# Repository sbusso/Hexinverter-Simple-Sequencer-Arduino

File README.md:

# Hexinverter-Simple-Sequencer-Arduino
Modified Version of Hexinverter Simple Seq, using 2 arduino nano boards intstead of the logic boards

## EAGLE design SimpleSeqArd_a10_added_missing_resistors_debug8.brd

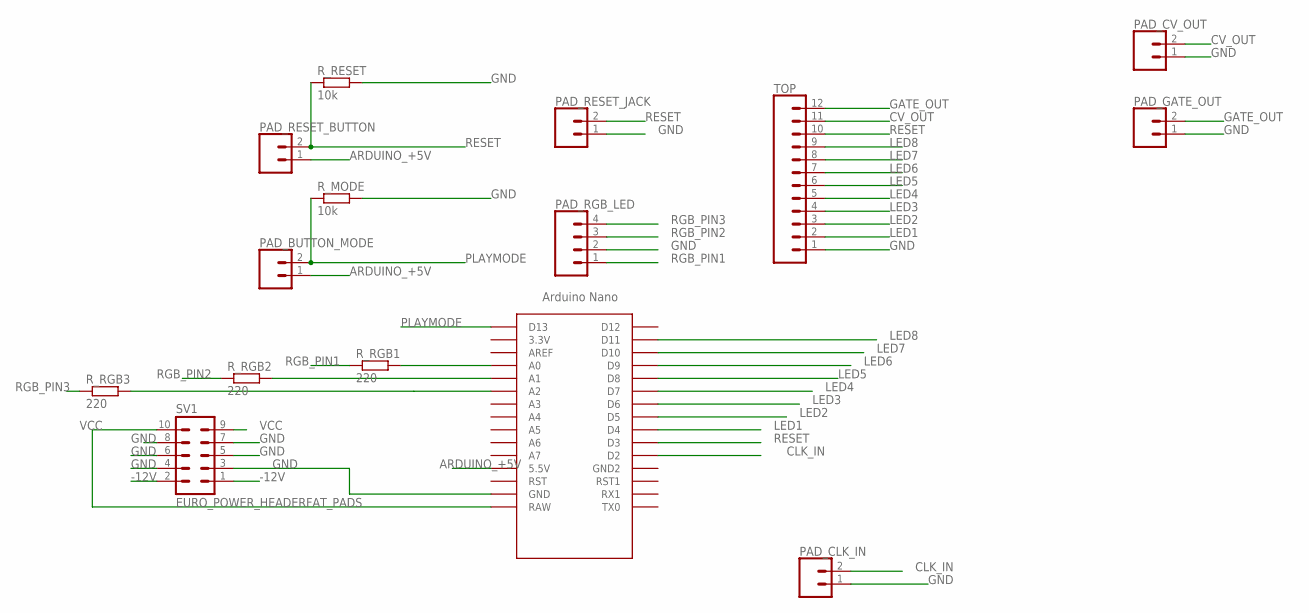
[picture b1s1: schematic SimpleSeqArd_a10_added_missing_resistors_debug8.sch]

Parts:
PAD_BUTTON_MODE: CONN_02PTH3; 1X02_LONGPADS
PAD_CLK_IN: CONN_02PTH3; 1X02_LONGPADS
PAD_CV_OUT: CONN_02PTH3; 1X02_LONGPADS
PAD_GATE_OUT: CONN_02PTH3; 1X02_LONGPADS
PAD_RESET_BUTTON: CONN_02PTH3; 1X02_LONGPADS
PAD_RESET_JACK: CONN_02PTH3; 1X02_LONGPADS
PAD_RGB_LED: CONN_04LONGPADS; 1X04_LONGPADS
R_MODE: 10k; VERTICAL_RESISTOR
R_RESET: 10k; VERTICAL_RESISTOR
R_RGB1, R_RGB2, R_RGB3: 220; VERTICAL_RESISTOR
SV1: EURO_POWER_HEADERFAT_PADS; EURO_PWR_HEADER_FAT
TOP: CONN_12LONGPADS; 1X12_LONGPADS
U$1: NANO

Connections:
-12V: SV1.1, SV1.2
ARDUINO_+5V: PAD_BUTTON_MODE.1, PAD_RESET_BUTTON.1, U$1.5V (5.5V)
CLK_IN: PAD_CLK_IN.2, U$1.D2
CV_OUT: PAD_CV_OUT.2, TOP.11
GATE_OUT: PAD_GATE_OUT.2, TOP.12
GND: PAD_CLK_IN.1, PAD_CV_OUT.1, PAD_GATE_OUT.1, PAD_RESET_JACK.1, PAD_RGB_LED.2, R_MODE.2, R_RESET.2, SV1.3, SV1.4, SV1.5, SV1.6, SV1.7, SV1.8, TOP.1, U$1.GND
LED1: TOP.2, U$1.D4
LED2: TOP.3, U$1.D5
LED3: TOP.4, U$1.D6
LED4: TOP.5, U$1.D7
LED5: TOP.6, U$1.D8
LED6: TOP.7, U$1.D9
LED7: TOP.8, U$1.D10
LED8: TOP.9, U$1.D11
unnamed: R_RGB1.2, U$1.A0
unnamed: R_RGB2.2, U$1.A1
unnamed: R_RGB3.2, U$1.A2
PLAYMODE: PAD_BUTTON_MODE.2, R_MODE.1, U$1.D13
RESET: PAD_RESET_BUTTON.2, PAD_RESET_JACK.2, R_RESET.1, TOP.10, U$1.D3
RGB_PIN1: PAD_RGB_LED.1, R_RGB1.1
RGB_PIN2: PAD_RGB_LED.3, R_RGB2.1
RGB_PIN3: PAD_RGB_LED.4, R_RGB3.1
VCC: SV1.9, SV1.10, U$1.RAW

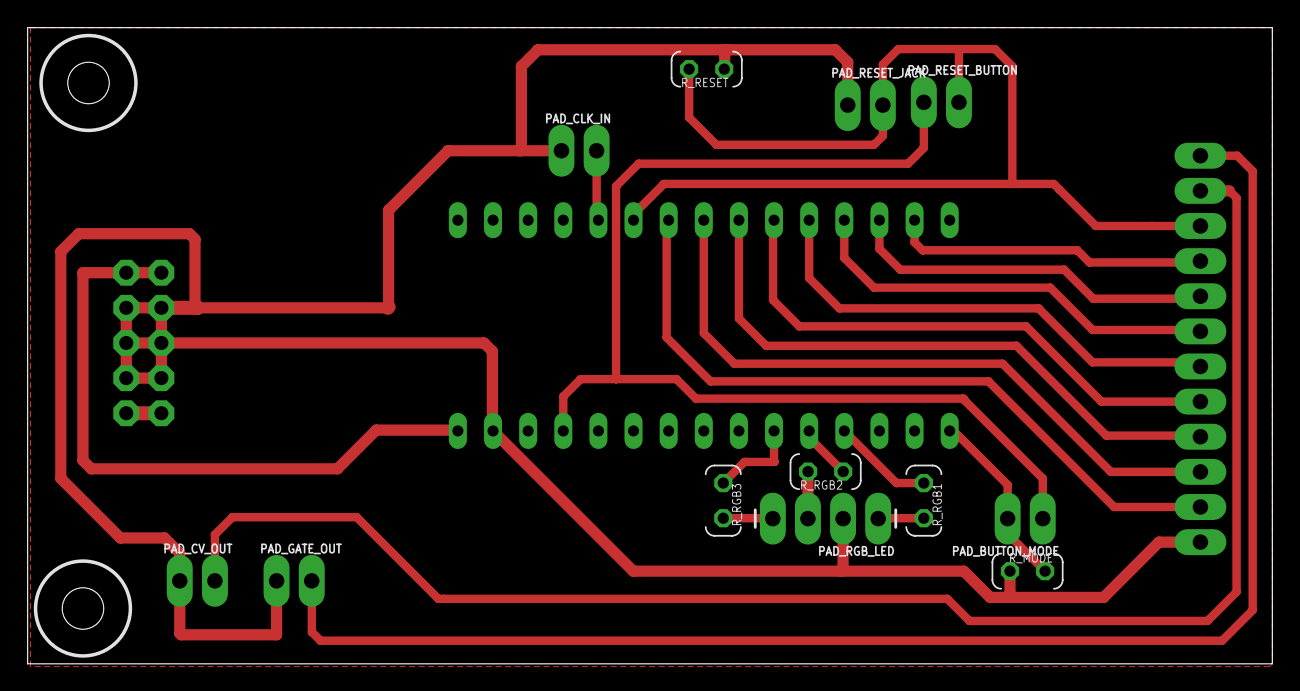
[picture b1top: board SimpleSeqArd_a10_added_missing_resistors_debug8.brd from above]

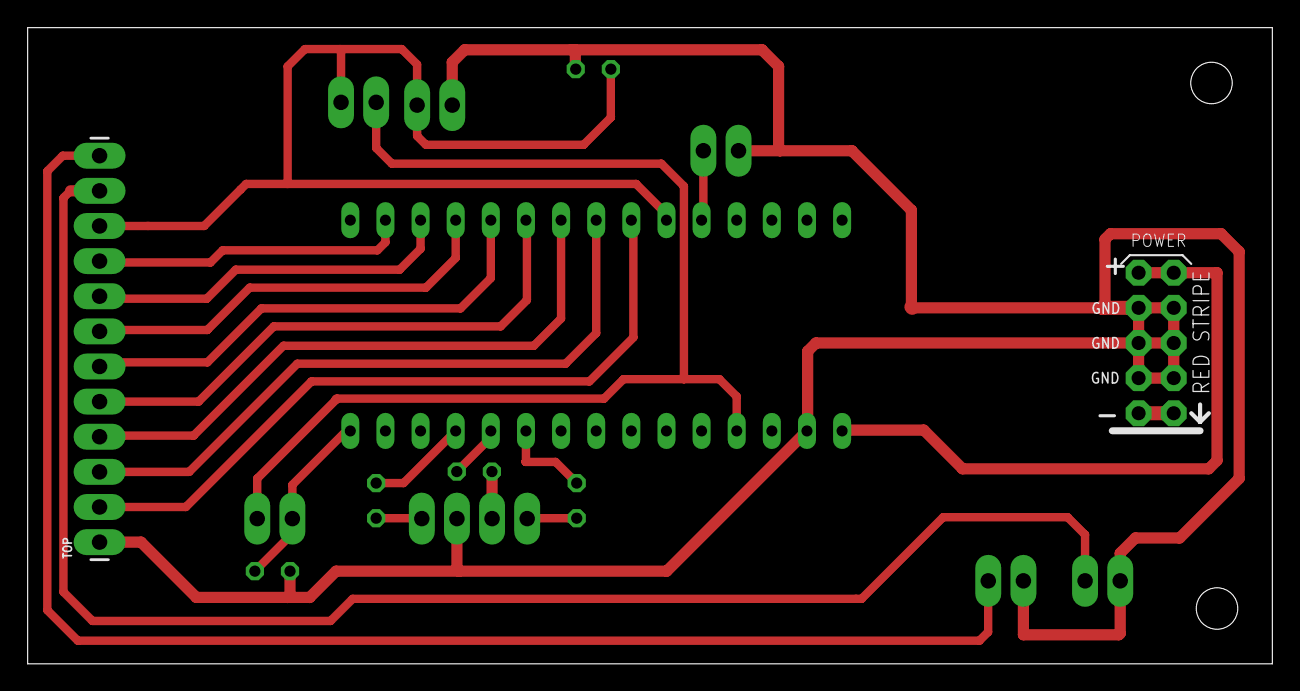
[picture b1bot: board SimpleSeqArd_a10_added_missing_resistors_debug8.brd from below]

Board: 2 copper layers, 90.0 x 46.0 mm, 17 parts (3 on the bottom side), 23 nets.

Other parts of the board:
H1, H2: DRIL-3

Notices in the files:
parts and their libraries:
SparkFun-Connectors: Licensing: Creative Commons ShareAlike 4.0 International - https://creativecommons.org/licenses/by-sa/4.0
